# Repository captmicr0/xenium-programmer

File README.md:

# OpenXenium JTAG and Flash Memory programmer
New smaller size board is less wasteful and has on-board buttons that actually work with the new script!  
LEDs are connected to different GPIOs than the original board, so **the old script will not work properly**.  
Plug the RPI and the OpenXenium modchip into their respective headers, and run the new script.  
The DETECT LED below the OpenXenium outline will turn on when a modchip is inserted.

### Raspberry PI:
- This has only been tested on PI Zero W so far.

-------------
## INSTALLING THE XENIUM PROGRAMMER

On the PI:
- Clone this repo by running: `git clone https://github.com/captmicr0/xenium-programmer`
- Then run: `./install`

## UPDATING XENIUM PROGRAMMER

On the PI:
- Pull the latest code with: `git pull`
- Then run: `./install` 

-------------
## PROGRAMMING A XENIUM CPLD AND FLASH MEMORY

- Connect to the PI or Omega via SSH or Serial terminal
- Run: `./xenium-programmer-small`
- On the board, press the BIOS button to write a new BIOS to the OpenXenium flash chip
- On the board, press the CPLD button to program the Xilinx CPLD on the OpenXenium.

**Note**: Pressing the BIOS button will flash a program onto the CPLD that allows you to  
write to the flash chip. This overwrites the OpenXenium firmware, so you must re-program  
the CPLD afterwards by pressing the CPLD button.

### SMALL PC BOARD

-------------
## CREDITS

- Koos du Preez - Creator (kdupreez@hotmail.com - Comments, improvements, critique, etc. is welcome!)
- James Bolding - Kick ass awesome hardware design and PCB!
- captmicr0 - Smaller board design and modified script for it.
- Ryzee119 -  OpenXenium Firmware and hardware and all round awesomeness!
- XC3SPROG - Not sure who to thank here, but the source code was pivotal in making this work!

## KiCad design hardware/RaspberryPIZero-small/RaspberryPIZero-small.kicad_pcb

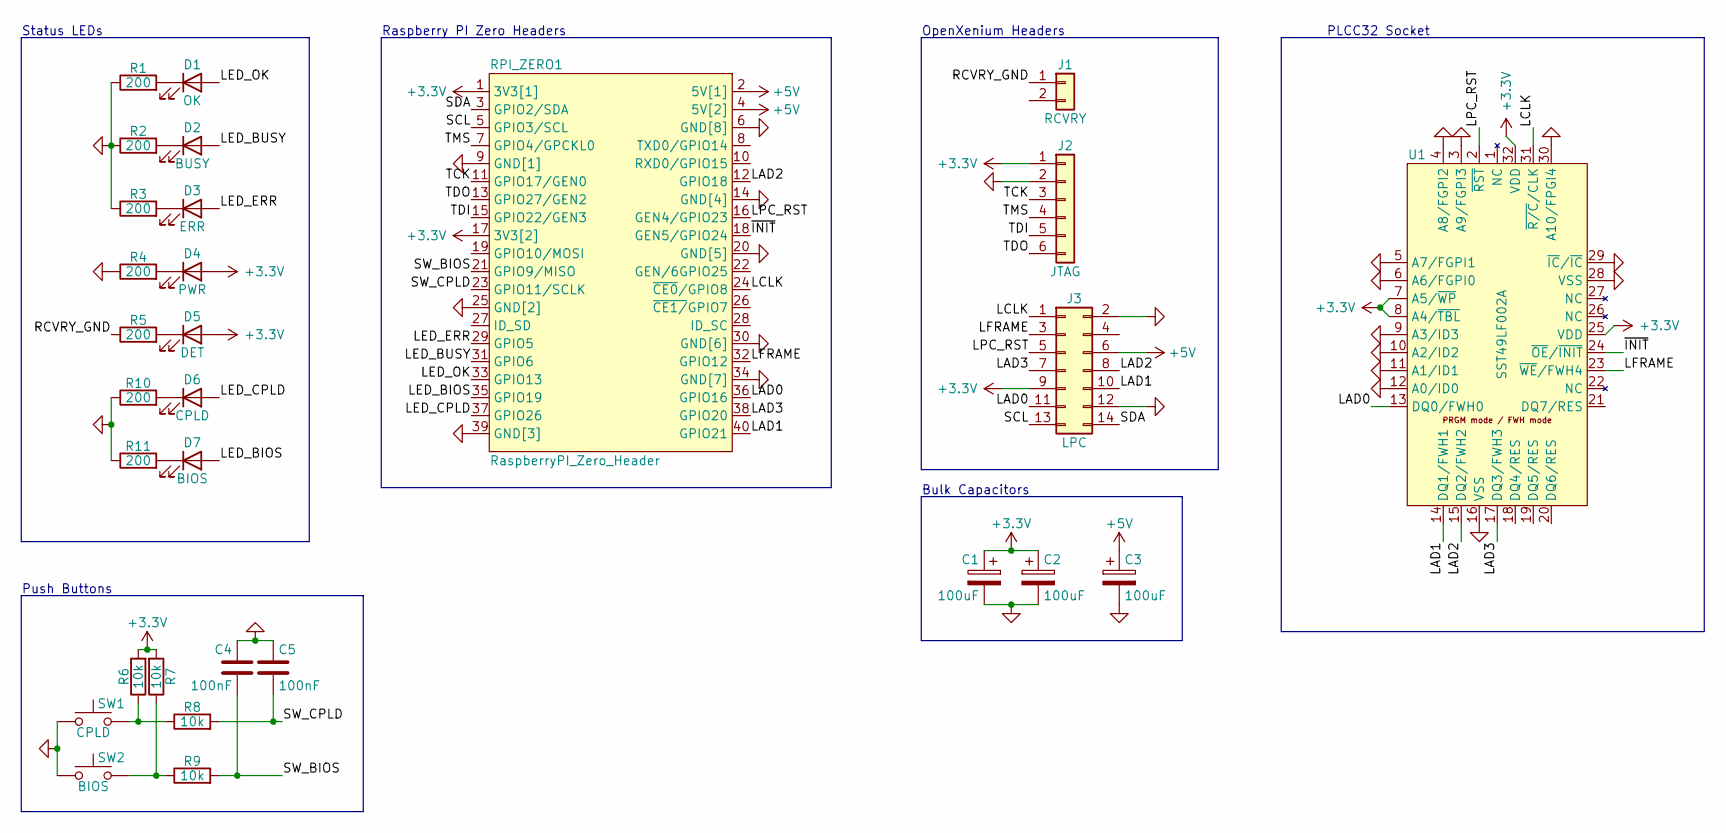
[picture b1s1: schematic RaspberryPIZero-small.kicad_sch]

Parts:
C1, C2, C3: 100uF; CP_EIA-3216-18_Kemet-A; MFR# CL31A107MQHNNNE; LCSC# C15008
C4, C5: 100nF; C_0603_1608Metric; MFR# CC0603KRX7R9BB104; LCSC# C14663
D1: OK; LED_0603_1608Metric; MFR# SZYY0603G; LCSC# C434420
D2: BUSY; LED_0603_1608Metric; MFR# SZYY0603O; LCSC# C434425
D3: ERR; LED_0603_1608Metric; MFR# SZYY0603R; LCSC# C434419
D4: PWR; LED_0603_1608Metric; MFR# SZYY0603B; LCSC# C434421
D5: DET; LED_0603_1608Metric; MFR# SZYY0603B; LCSC# C434421
D6: CPLD; LED_0603_1608Metric; MFR# SZYY0603O; LCSC# C434425
D7: BIOS; LED_0603_1608Metric; MFR# SZYY0603O; LCSC# C434425
J1: RCVRY; PinHeader_1x02_P2.54mm_Vertical
J2: JTAG; PinHeader_1x06_P2.54mm_Vertical; MFR# C2337; LCSC# C2337
J3: LPC; PinHeader_2x07_P2.54mm_Vertical; MFR# C57369; LCSC# C57369
R1, R2, R3, R4, R5, R10, R11: 200; R_0603_1608Metric; MFR# 0603WAF2000T5E; LCSC# C8218
R6, R7, R8, R9: 10k; R_0603_1608Metric; MFR# 0603WAF1002T5E; LCSC# C25804
RPI_ZERO1: RaspberryPI_Zero_Header; RaspberryPI_Zero; MFR# X6521FV-2x10-C85D32; LCSC# C718226
SW1: CPLD; SW_SPST_PTS645; MFR# PTS645SM70SMTR92LFS; LCSC# C221883
SW2: BIOS; SW_SPST_PTS645; MFR# PTS645SM70SMTR92LFS; LCSC# C221883
U1: SST49LF002A; PLCC-32-SOCKET-SMT

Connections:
+3V3: C1.1, C2.1, D4.2 (A), D5.2 (A), J2.1, J3.9, R6.2, R7.2, RPI_ZERO1.1 (3V3[1]), RPI_ZERO1.17 (3V3[2]), U1.7 (A5/~WP), U1.8 (A4/~TBL), U1.25 (VDD), U1.32 (VDD)
+5V: C3.1, J3.6, RPI_ZERO1.2 (5V[1]), RPI_ZERO1.4 (5V[2])
/LAD0: J3.11, RPI_ZERO1.36 (GPIO16), U1.13 (DQ0/FWH0)
/LAD1: J3.10, RPI_ZERO1.40 (GPIO21), U1.14 (DQ1/FWH1)
/LAD2: J3.8, RPI_ZERO1.12 (GPIO18), U1.15 (DQ2/FWH2)
/LAD3: J3.7, RPI_ZERO1.38 (GPIO20), U1.17 (DQ3/FWH3)
/LCLK: J3.1, RPI_ZERO1.24 (~CE0/GPIO8), U1.31 (~R/C/CLK)
/LED_BIOS: D7.2 (A), RPI_ZERO1.35 (GPIO19)
/LED_BUSY: D2.2 (A), RPI_ZERO1.31 (GPIO6)
/LED_CPLD: D6.2 (A), RPI_ZERO1.37 (GPIO26)
/LED_ERR: D3.2 (A), RPI_ZERO1.29 (GPIO5)
/LED_OK: D1.2 (A), RPI_ZERO1.33 (GPIO13)
/LFRAME: J3.3, RPI_ZERO1.32 (GPIO12), U1.23 (~WE/FWH4)
/LPC_RST: J3.5, RPI_ZERO1.16 (GEN4/GPIO23), U1.2 (~RST)
/RCVRY_GND: J1.1, R5.1
/SCL: J3.13, RPI_ZERO1.5 (GPIO3/SCL)
/SDA: J3.14, RPI_ZERO1.3 (GPIO2/SDA)
/SW_BIOS: C4.2, R9.2, RPI_ZERO1.21 (GPIO9/MISO)
/SW_CPLD: C5.2, R8.2, RPI_ZERO1.23 (GPIO11/SCLK)
/TCK: J2.3, RPI_ZERO1.11 (GPIO17/GEN0)
/TDI: J2.5, RPI_ZERO1.15 (GPIO22/GEN3)
/TDO: J2.6, RPI_ZERO1.13 (GPIO27/GEN2)
/TMS: J2.4, RPI_ZERO1.7 (GPIO4/GPCKL0)
/~INIT: RPI_ZERO1.18 (GEN5/GPIO24), U1.24 (~OE/~INIT)
GND: C1.2, C2.2, C3.2, C4.1, C5.1, J2.2, J3.2, J3.12, R1.1, R2.1, R3.1, R4.1, R10.1, R11.1, RPI_ZERO1.6 (GND[8]), RPI_ZERO1.9 (GND[1]), RPI_ZERO1.14 (GND[4]), RPI_ZERO1.20 (GND[5]), RPI_ZERO1.25 (GND[2]), RPI_ZERO1.30 (GND[6]), RPI_ZERO1.34 (GND[7]), RPI_ZERO1.39 (GND[3]), SW1.1, SW2.1, U1.3 (A9/FGPI3), U1.4 (A8/FGPI2), U1.5 (A7/FGPI1), U1.6 (A6/FGPI0), U1.9 (A3/ID3), U1.10 (A2/ID2), U1.11 (A1/ID1), U1.12 (A0/ID0), U1.16 (VSS), U1.28 (VSS), U1.29 (~IC/~IC), U1.30 (A10/FPGI4)
unnamed: D1.1 (K), R1.2
unnamed: D2.1 (K), R2.2
unnamed: D3.1 (K), R3.2
unnamed: D4.1 (K), R4.2
unnamed: D5.1 (K), R5.2
unnamed: D6.1 (K), R10.2
unnamed: D7.1 (K), R11.2
unnamed: R6.1, R8.1, SW1.2
unnamed: R7.1, R9.1, SW2.2

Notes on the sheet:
OpenXenium Headers
Bulk Capacitors
PLCC32 Socket
Status LEDs
Push Buttons
Raspberry PI Zero Headers

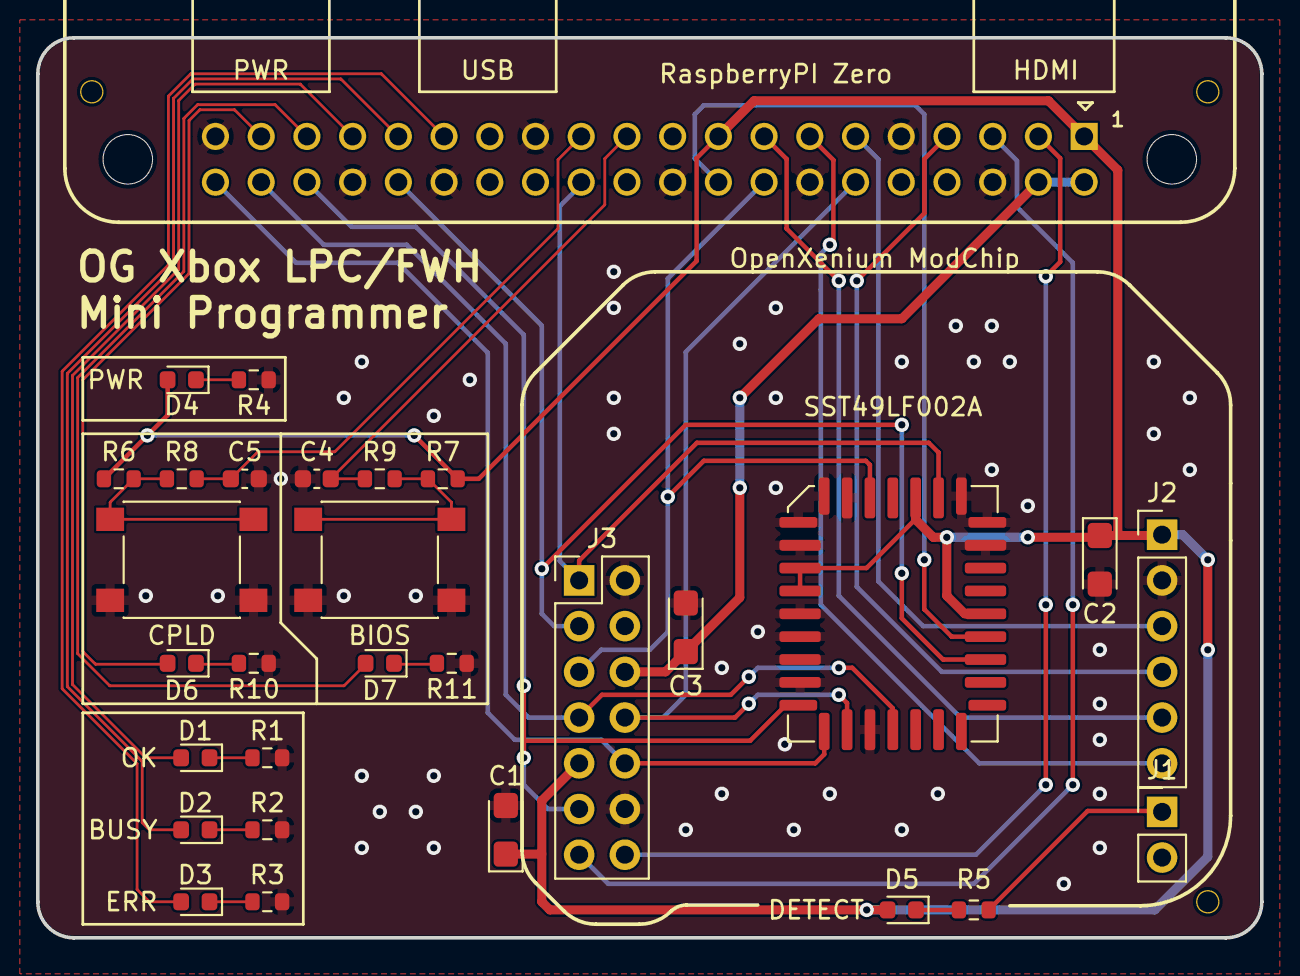
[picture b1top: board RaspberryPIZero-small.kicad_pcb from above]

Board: 2 copper layers, 68.0 x 50.0 mm, 30 parts (0 on the bottom side), 34 nets.

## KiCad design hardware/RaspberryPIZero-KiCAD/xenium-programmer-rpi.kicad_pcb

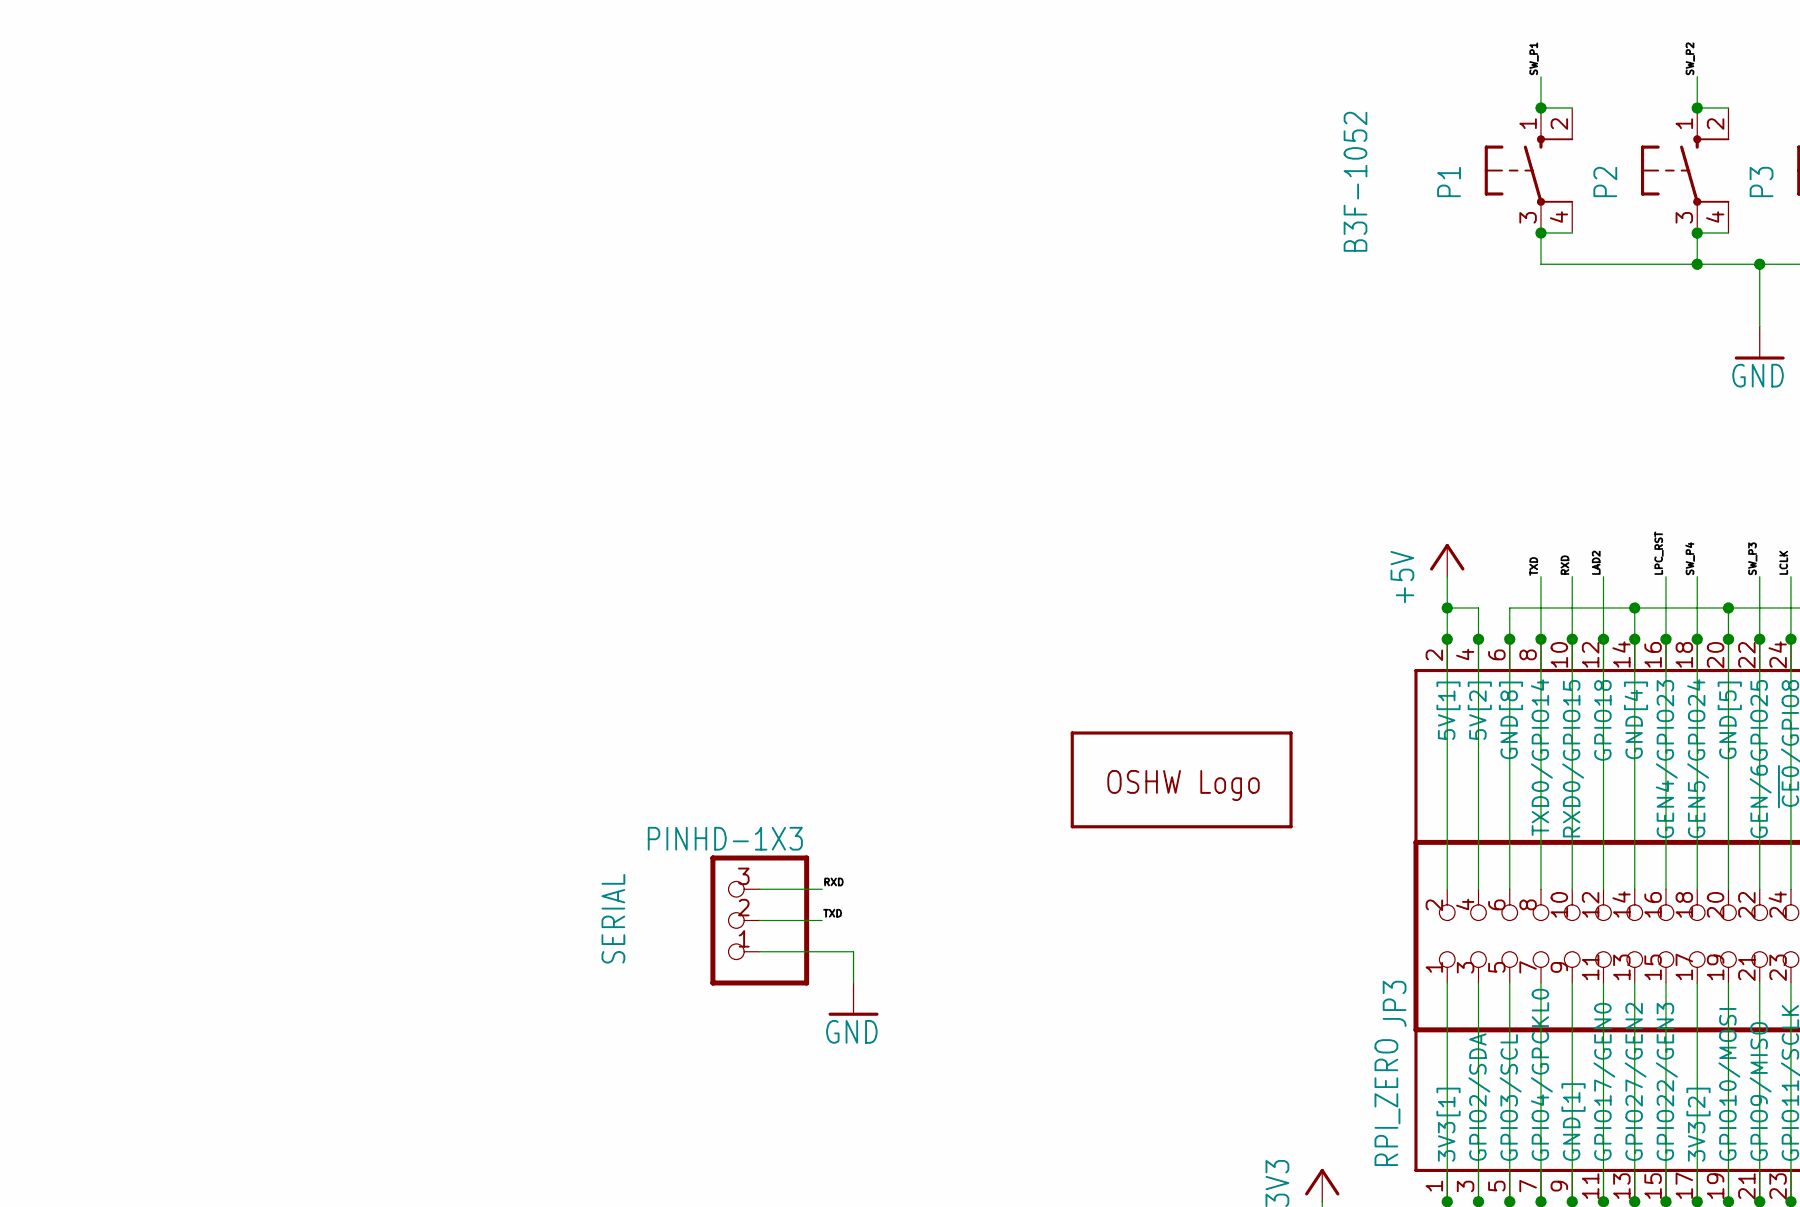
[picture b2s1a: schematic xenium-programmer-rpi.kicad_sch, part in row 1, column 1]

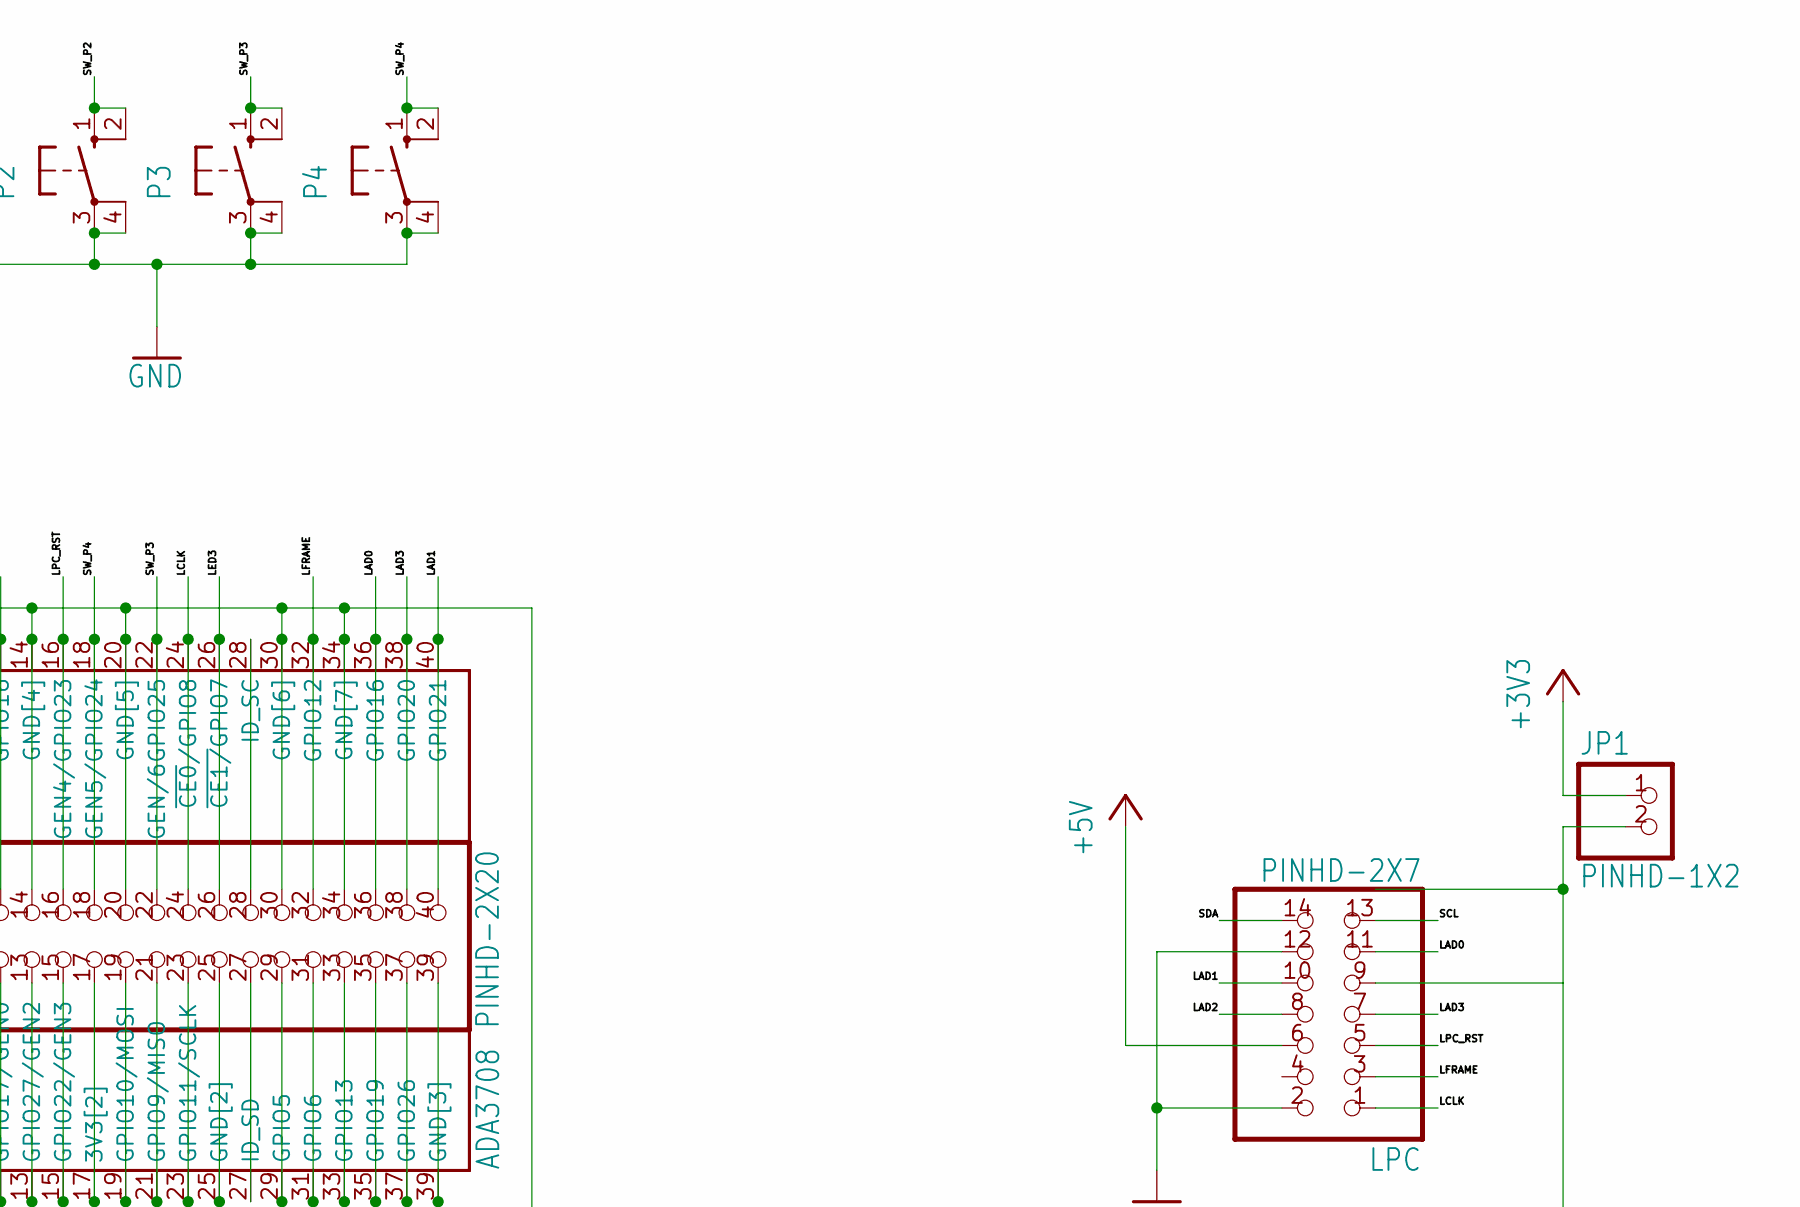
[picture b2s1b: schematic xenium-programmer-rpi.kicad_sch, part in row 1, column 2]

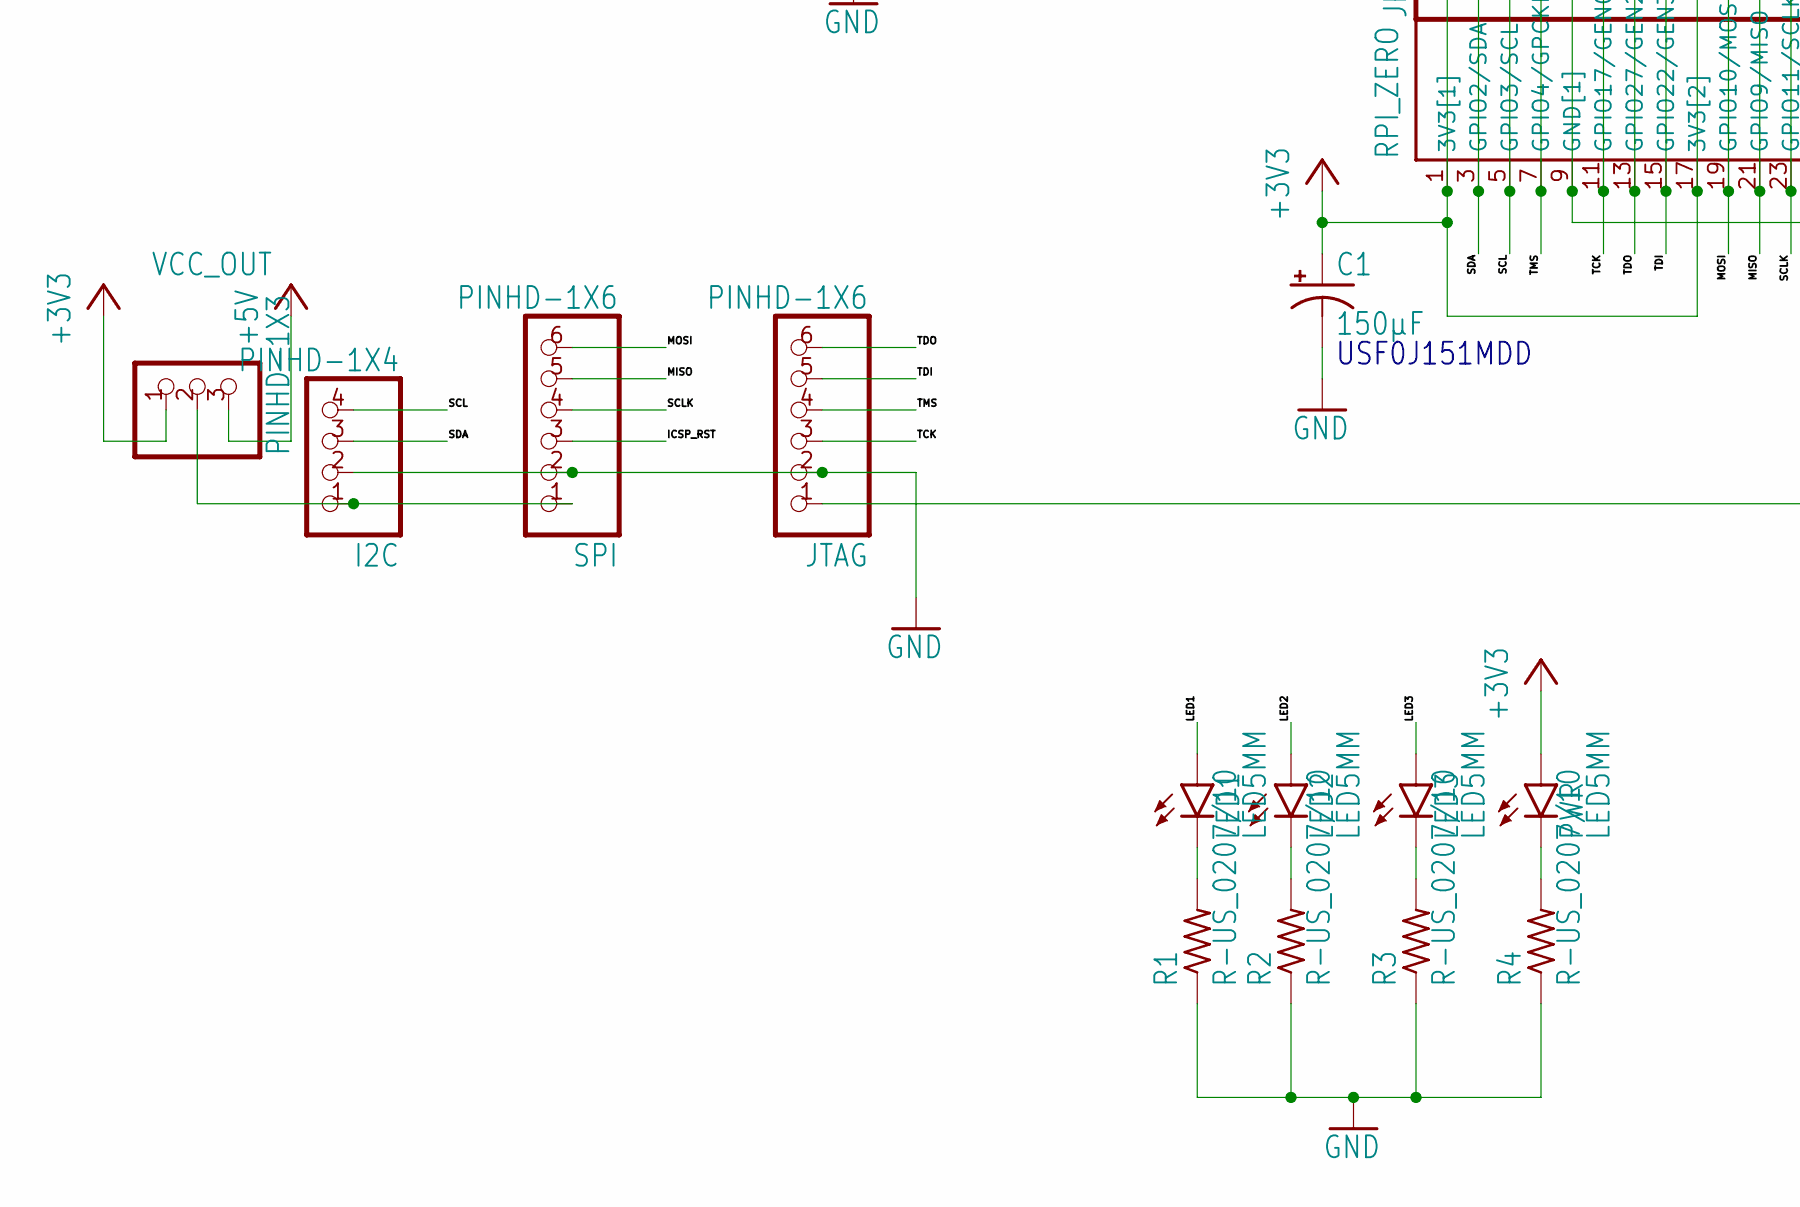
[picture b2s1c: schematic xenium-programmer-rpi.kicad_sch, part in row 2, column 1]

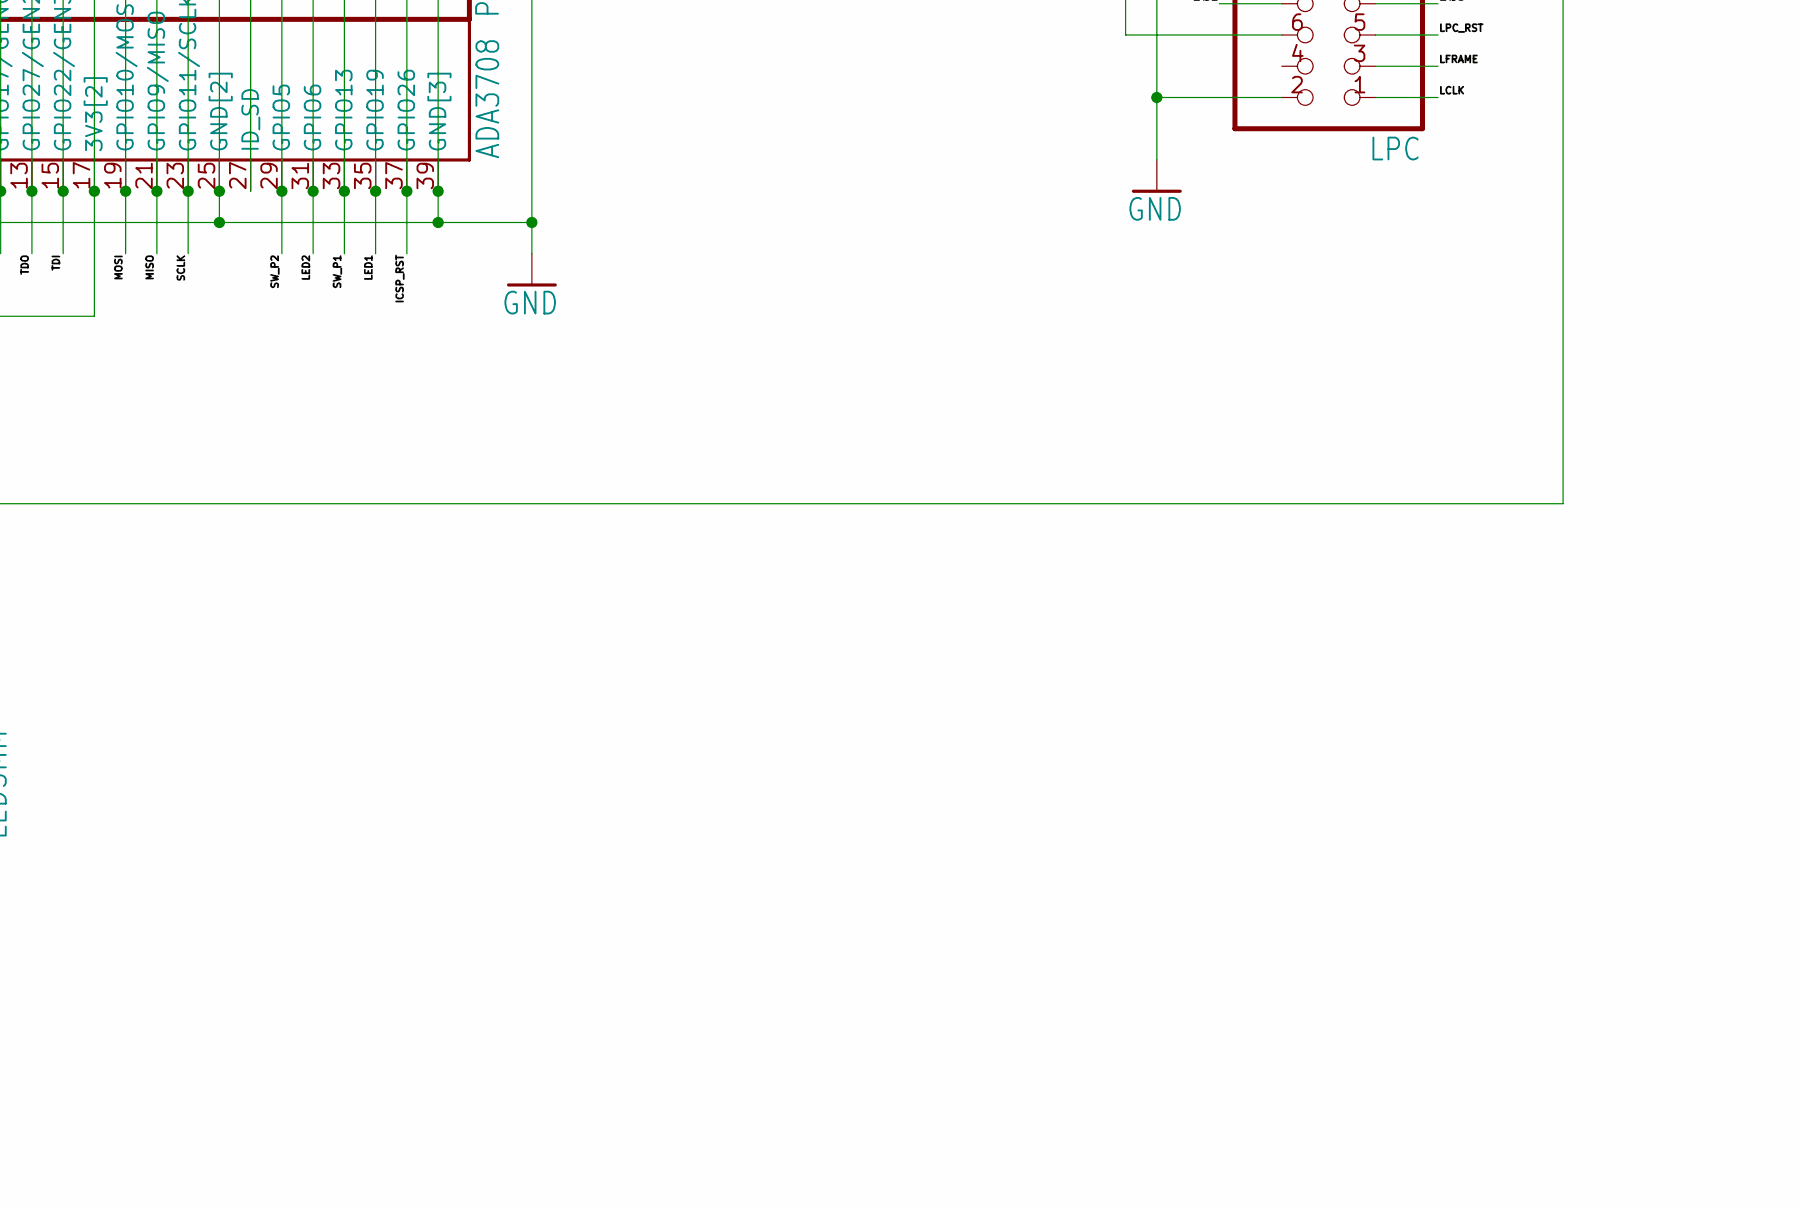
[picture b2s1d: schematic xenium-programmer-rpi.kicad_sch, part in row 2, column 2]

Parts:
C1: 150µF; E3,5-8
GOLD_ORB_SM1: OSHWLOGOLOGO8MM; OSHW_8MM
I2C: PINHD-1X4; 1X04
JP1: PINHD-1X2; 1X02
JP3: PINHD-2X20; 2X20
JTAG: PINHD-1X6; 1X06
LED1, LED2, LED3: LED5MM
LPC: PINHD-2X7; 2X07
P1, P2, P3, P4: B3F-1052; B3F-10XX
PWR: LED5MM
R1, R2, R3, R4: R-US_0207/10; 0207_10
RPI_ZERO: ADA3708; ADA3708_RPI-ZERO
SERIAL: PINHD-1X3; 1X03
SPI: PINHD-1X6; 1X06
VCC_OUT: PINHD-1X3; 1X03

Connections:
+3V3: C1.+, JP1.1, JP3.1, JP3.17, PWR.A, RPI_ZERO.1 (3V3[1]), RPI_ZERO.17 (3V3[2]), VCC_OUT.1
+5V: JP3.2, JP3.4, LPC.6, RPI_ZERO.2 (5V[1]), RPI_ZERO.4 (5V[2]), VCC_OUT.3
GND: C1.-, I2C.2, JP3.6, JP3.9, JP3.14, JP3.20, JP3.25, JP3.30, JP3.34, JP3.39, JTAG.2, LPC.2, LPC.12, P1.3, P1.4 (P1), P2.3, P2.4 (P1), P3.3, P3.4 (P1), P4.3, P4.4 (P1), R1.1, R2.1, R3.1, R4.1, RPI_ZERO.6 (GND[8]), RPI_ZERO.9 (GND[1]), RPI_ZERO.14 (GND[4]), RPI_ZERO.20 (GND[5]), RPI_ZERO.25 (GND[2]), RPI_ZERO.30 (GND[6]), RPI_ZERO.34 (GND[7]), RPI_ZERO.39 (GND[3]), SERIAL.1, SPI.2
ICSP_RST: JP3.37, RPI_ZERO.37 (GPIO26), SPI.3
LAD0: JP3.36, LPC.11, RPI_ZERO.36 (GPIO16)
LAD1: JP3.40, LPC.10, RPI_ZERO.40 (GPIO21)
LAD2: JP3.12, LPC.8, RPI_ZERO.12 (GPIO18)
LAD3: JP3.38, LPC.7, RPI_ZERO.38 (GPIO20)
LCLK: JP3.24, LPC.1, RPI_ZERO.24 (~CE0/GPIO8)
LED1: JP3.35, LED1.A, RPI_ZERO.35 (GPIO19)
LED2: JP3.31, LED2.A, RPI_ZERO.31 (GPIO6)
LED3: JP3.26, LED3.A, RPI_ZERO.26 (~CE1/GPIO7)
LFRAME: JP3.32, LPC.3, RPI_ZERO.32 (GPIO12)
LPC_RST: JP3.16, LPC.5, RPI_ZERO.16 (GEN4/GPIO23)
MISO: JP3.21, RPI_ZERO.21 (GPIO9/MISO), SPI.5
MOSI: JP3.19, RPI_ZERO.19 (GPIO10/MOSI), SPI.6
unnamed: LED1.K (C), R1.2
unnamed: JP3.27, RPI_ZERO.27 (ID_SD)
unnamed: LED2.K (C), R2.2
unnamed: LED3.K (C), R3.2
unnamed: PWR.K (C), R4.2
unnamed: JP1.2, JTAG.1, LPC.9
unnamed: JP3.28, RPI_ZERO.28 (ID_SC)
RXD: JP3.10, RPI_ZERO.10 (RXD0/GPIO15), SERIAL.3
SCL: I2C.4, JP3.5, LPC.13, RPI_ZERO.5 (GPIO3/SCL)
SCLK: JP3.23, RPI_ZERO.23 (GPIO11/SCLK), SPI.4
SDA: I2C.3, JP3.3, LPC.14, RPI_ZERO.3 (GPIO2/SDA)
SW_P1: JP3.33, P1.1 (S), P1.2 (S1), RPI_ZERO.33 (GPIO13)
SW_P2: JP3.29, P2.1 (S), P2.2 (S1), RPI_ZERO.29 (GPIO5)
SW_P3: JP3.22, P3.1 (S), P3.2 (S1), RPI_ZERO.22 (GEN/6GPIO25)
SW_P4: JP3.18, P4.1 (S), P4.2 (S1), RPI_ZERO.18 (GEN5/GPIO24)
TCK: JP3.11, JTAG.3, RPI_ZERO.11 (GPIO17/GEN0)
TDI: JP3.15, JTAG.5, RPI_ZERO.15 (GPIO22/GEN3)
TDO: JP3.13, JTAG.6, RPI_ZERO.13 (GPIO27/GEN2)
TMS: JP3.7, JTAG.4, RPI_ZERO.7 (GPIO4/GPCKL0)
TXD: JP3.8, RPI_ZERO.8 (TXD0/GPIO14), SERIAL.2
VCC_OUT: I2C.1, SPI.1, VCC_OUT.2

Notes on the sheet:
USF0J151MDD

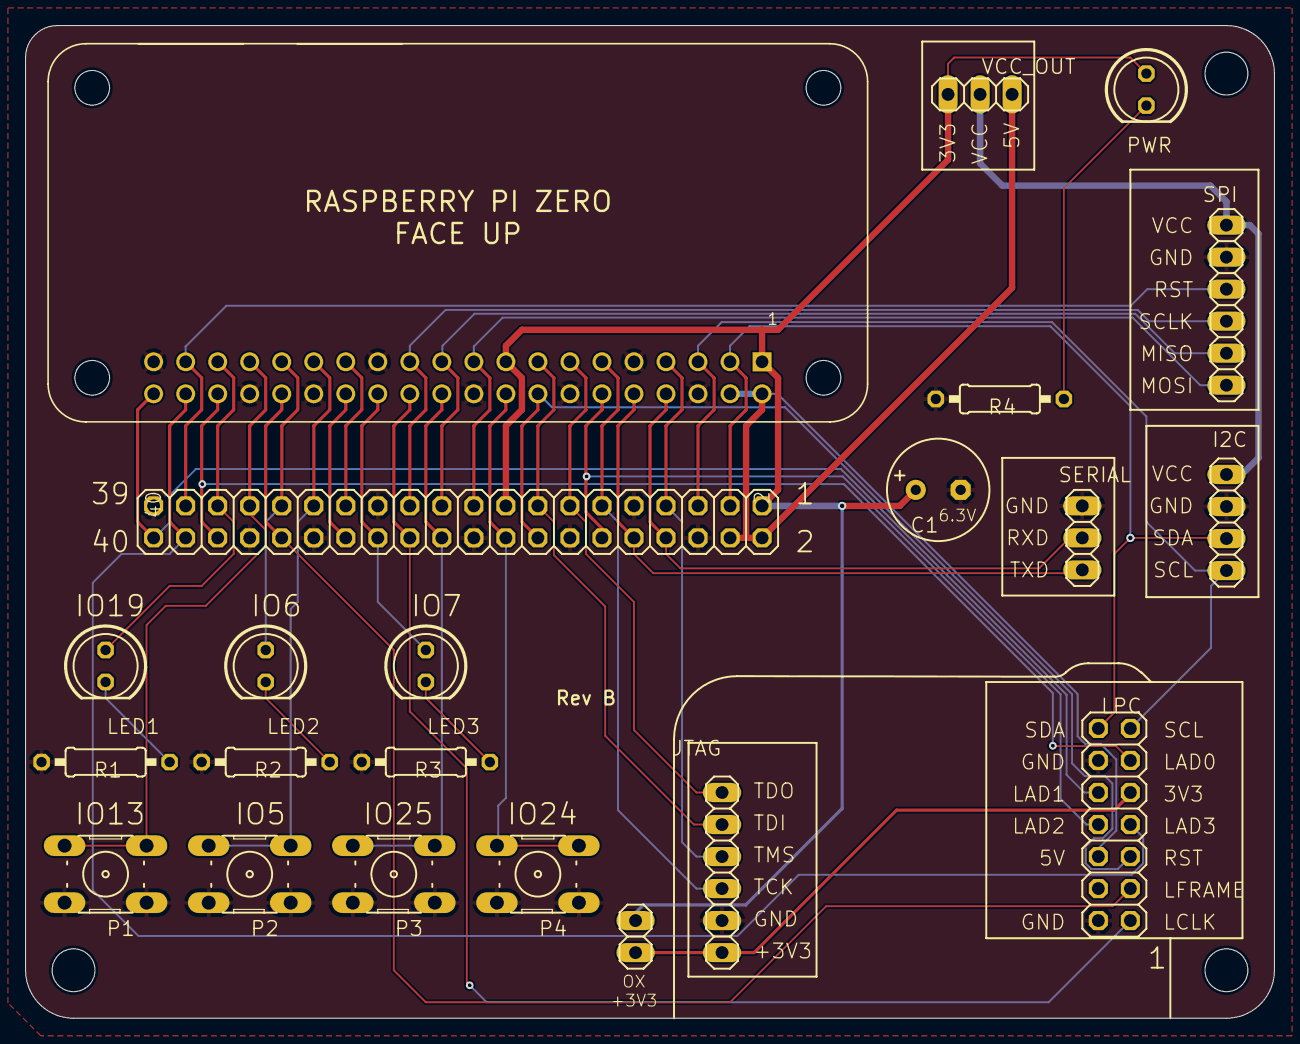
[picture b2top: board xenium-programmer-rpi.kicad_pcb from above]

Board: 2 copper layers, 99.1 x 78.7 mm, 26 parts (1 on the bottom side), 37 nets.

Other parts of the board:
@HOLE0, @HOLE1, @HOLE2: (no value)

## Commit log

2022-07-08 converted to KiCAD, added SFF board, added script for SFF board
2022-07-08 added tooling holes to pcb & create JLCPCB manufacturing files
2022-08-14 modified board to support flashing 49LF002A

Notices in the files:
hardware/RaspberryPIZero-KiCAD/xenium-programmer-rpi.kicad_pcb:
Released under
CERN OHL v1.2
